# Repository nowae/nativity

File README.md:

# nativity
Project of a technological nativity scene for my home

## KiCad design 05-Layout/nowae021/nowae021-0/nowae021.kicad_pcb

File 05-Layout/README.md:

# nativity

In this folder you can find the boards design files of project.
* NOWAE021 - Fireplace node

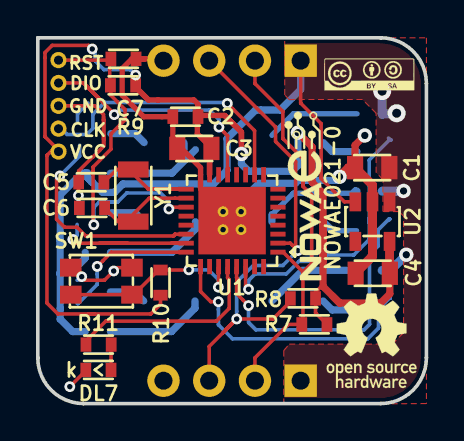
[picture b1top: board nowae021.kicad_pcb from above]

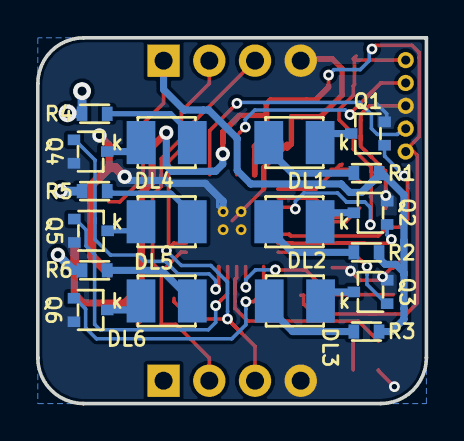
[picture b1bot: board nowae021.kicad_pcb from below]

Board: 2 copper layers, 21.6 x 20.3 mm, 38 parts (19 on the bottom side), 31 nets.

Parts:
C1: 1u; CAPACITOR-0805
C2, C7: 100n; CAPACITOR-0603
C3: 10u; CAPACITOR-0805
C4: 2u2; CAPACITOR-0805
C5, C6: 15p; CAPACITOR-0603
DL1, DL3, DL5: YELLOW; LED-WURTH-WL_SMTW_3528
DL2: RED; LED-WURTH-WL_SMTW_3528
DL4, DL6: AMBER; LED-WURTH-WL_SMTW_3528
DL7: GREEN; LED-0603
P1, P2: NVT_BUS; CONN-STRIP-4x1-2.54_NOSILK
P3: SWD; CONN-STRIP-5x1-1.27
Q1, Q2, Q3, Q4, Q5, Q6: PDTC123EU; SOT323-3
R1, R2, R3, R4, R5, R6: 1k; RESISTOR-0603
R7, R8: 4k7; RESISTOR-0603
R9, R10: 10k; RESISTOR-0603
R11: 270; RESISTOR-0603
SW1: BUTTON-WE_434153017835; BUTTON-WE-434153017835
U1: MKL15Z128VFM4; QFN32_5x5_0.5_32+1
U2: TPS70933DBV; SOT23-5
Y1: 32768; CRYSTAL-1206

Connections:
+3.3V: C2.1, C3.1, C4.1, P3.1, R7.1, R8.1, R9.1, R10.1, U1.15, U2.5
+VIN: C1.1, P1.1, P2.1, R1.1, R2.1, R3.1, R4.1, R5.1, R6.1, U2.1, U2.3
/ADDR_PROG: R10.2, SW1.2, SW1.4, U1.27
/FIRE_LED1: Q1.1, U1.22
/FIRE_LED2: Q2.1, U1.23
/FIRE_LED3: Q3.1, U1.24
/FIRE_LED4: Q4.1, U1.30
/FIRE_LED5: Q5.1, U1.29
/FIRE_LED6: Q6.1, U1.25
/MCU_STATUS: R11.2, U1.28
/NTV_COMM_SCL: P1.3, P2.3, R8.2, U1.2
/NTV_COMM_SDA: P1.2, P2.2, R7.2, U1.1
/RESET: C7.1, P3.5, R9.2, U1.19
/SWCLK: P3.2, U1.10
/SWDIO: P3.4, U1.13
GND: C1.2, C2.2, C3.2, C4.2, C5.2, C6.2, C7.2, DL7.2, P1.4, P2.4, P3.3, Q1.2, Q2.2, Q3.2, Q4.2, Q5.2, Q6.2, SW1.1, SW1.3, U1.16, U1.EP, U2.2
unnamed: C5.1, U1.17, Y1.1
unnamed: C6.1, U1.18, Y1.2
unnamed: DL1.1, Q1.3
unnamed: DL1.2, R1.2
unnamed: DL2.1, Q2.3
unnamed: DL2.2, R2.2
unnamed: DL3.1, Q3.3
unnamed: DL3.2, R3.2
unnamed: DL4.1, Q4.3
unnamed: DL4.2, R4.2
unnamed: DL5.1, Q5.3
unnamed: DL5.2, R5.2
unnamed: DL6.1, Q6.3
unnamed: DL6.2, R6.2
unnamed: DL7.1, R11.1

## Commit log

2018-10-29 Added project structure
2018-10-29 Added kicad project
2018-10-31 Added microcontroller (nowae021-0)
2018-11-04 WiP on schematic (nowae021-0)
2018-11-06 WiP schematic: added voltage regulator (nowae021-0)
2018-11-06 WiP shematic: small improvements (nowae021-0)
2018-11-07 Added transistor on each fire leds (nowae021-0)
2018-11-07 Added address programming button and center all the schematic (nowae021-0)
2018-11-07 Added MCU_STATUS led and RESET resistor and capacitor (nowae021-0)
2018-11-07 Changed fire leds with bigger one (nowae021-0)
2018-11-07 Annotate schematic (nowae021-0)
2018-11-08 WiP PCB components placement (nowae021-0)
2018-11-08 WiP routing (nowae021-0)
2018-11-09 WiP routing... is very hard with only two layer!
2018-11-12 Deleted debug connector. Wip routing.
2018-11-13 Added 2.54mm on width. WiP routing.
2018-11-13 Routing ended! (nowae021-0)
2018-11-14 Fixed fabrication informations (nowae021-0)
2018-11-14 Added license logos
2018-11-14 Added BOM (nowae021-0)
2018-11-14 Fixed worksheet informations and added schematic print file
2018-11-14 WiP assembly documentations (nowae021-0)
2018-11-20 Fixed error in led direction (nowae021-0)
2018-11-20 Changed debug connetor to increase the robustness of copper (nowae021-0)
2018-11-20 Small fix on PCB file
2018-11-20 Added archive with gerber files (nowae021-0)
2018-11-21 Removed castellated holes from the PCB... it is not useful in this project and it is o expensive!
2018-11-21 Added new gerber file archive without castellated holes (nowae021-0)
